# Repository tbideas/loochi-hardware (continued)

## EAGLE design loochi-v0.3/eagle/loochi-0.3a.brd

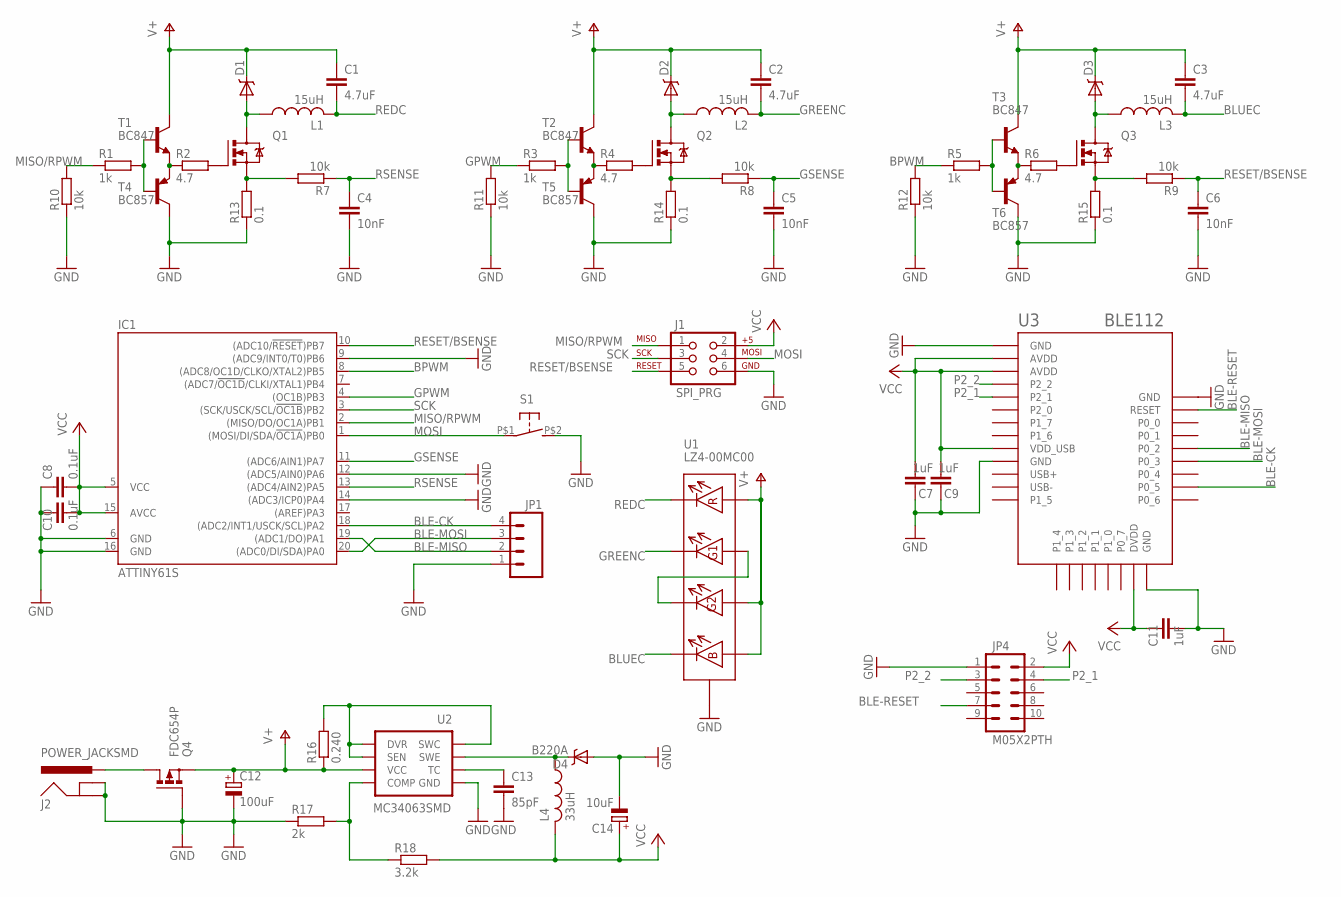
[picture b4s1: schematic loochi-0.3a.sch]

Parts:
C1, C2, C3: 4.7uF; C0805
C4, C5, C6: 10nF; C0805
C7, C9, C11: 1uF; C0805
C8, C10: 0.1uF; C0805
C12: 100uF; PANASONIC_D
C13: 85pF; C0805
C14: 10uF; UD-4X5,8_NICHICON
D1, D2, D3: PMEG4010CEH; SOD123F
D4: B220A; SMA-DIODE-BIG
IC1: ATTINY61S; SO20L
J1: SPI_PRG; 2X3-NS
J2: POWER_JACKSMD; POWER_JACK_SMD
JP1: M04PTH; 1X04
JP4: M05X2PTH; AVR_ICSP
L1, L2, L3: 15uH; BOURNS-6045
L4: 33uH; BOURNS-6045
Q1, Q2, Q3: PMN25ENSOT457; SOT457
Q4: FDC654P; SUPERSOT6
R1, R3, R5: 1k; R0805
R2, R4, R6: 4.7; R0805
R7, R8, R9, R10, R11, R12: 10k; R0805
R13, R14, R15: 0.1; R0805
R16: 0.240; R0805
R17: 2k; R0805
R18: 3.2k; R0805
S1: ALPS-SKRK39X29; ALPS-SKRK-39X29
T1, T2, T3: BC847; SOT23
T4, T5, T6: BC857; SOT23-BEC
U1: LZ4-00MC00
U2: MC34063SMD; SO08
U3: BLE112; SF-BLUEGIGA_BLE112-A

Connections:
BLE-CK: IC1.18 ((ADC2/INT1/USCK/SCL)PA2), JP1.4, U3.P0_5
BLE-MISO: IC1.19 ((ADC1/DO)PA1), JP1.2, U3.P0_2
BLE-MOSI: IC1.20 ((ADC0/DI/SDA)PA0), JP1.3, U3.P0_3
BLE-RESET: JP4.7, U3.RESET
BLUEC: C3.2, L3.P$2 (2), U1.P$8
BPWM: IC1.8 ((ADC8/OC1D/CLKO/XTAL2)PB5), R5.1, R12.2
GND: C4.2, C5.2, C6.2, C7.1, C8.1, C9.1, C10.1, C11.2, C12.-, C13.2, C14.-, D4.A, IC1.6 (GND), IC1.9 ((ADC9/INT0/T0)PB6), IC1.12 ((ADC5/AIN0)PA6), IC1.14 ((ADC3/ICP0)PA4), IC1.16 (GND), J1.6, J2.GND (GNDBREAK), J2.P$4 (GND), JP1.1, JP4.1, Q4.P$3 (G), R10.1, R11.1, R12.1, R13.1, R14.1, R15.1, R17.1, S1.P$2 (S), T4.C, T5.C, T6.C, U1.THERMAL, U1.THERMAL-VIA (THERMAL), U1.THERMAL-VIA2 (THERMAL), U2.4 (GND), U3.GND1 (GND), U3.GND2 (GND), U3.GND3 (GND), U3.GND4 (GND)
GPWM: IC1.4 ((OC1B)PB3), R3.1, R11.2
GREENC: C2.2, L2.P$2 (2), U1.P$6
GSENSE: C5.1, IC1.11 ((ADC6/AIN1)PA7), R8.1
MISO/RPWM: IC1.2 ((MISO/DO/OC1A)PB1), J1.1, R1.1, R10.2
MOSI: IC1.1 ((MOSI/DI/SDA/!OC1A!)PB0), J1.4, S1.P$1
unnamed: U1.P$1, U1.P$5
unnamed: R2.1, T1.2 (E), T4.E
unnamed: R1.2, T1.1 (B), T4.B
unnamed: Q1.P$3 (G), R2.2
unnamed: Q1.P$4 (S), R7.2, R13.2
unnamed: D1.P$A (A), L1.P$1 (1), Q1.P$1 (D), Q1.P$2 (D), Q1.P$5 (D), Q1.P$6 (D)
unnamed: R4.1, T2.2 (E), T5.E
unnamed: J2.VIN0 (PWR), J2.VIN1 (PWR), Q4.P$1 (D), Q4.P$2 (D), Q4.P$5 (D), Q4.P$6 (D)
unnamed: R3.2, T2.1 (B), T5.B
unnamed: Q2.P$3 (G), R4.2
unnamed: D2.P$A (A), L2.P$1 (1), Q2.P$1 (D), Q2.P$2 (D), Q2.P$5 (D), Q2.P$6 (D)
unnamed: R16.2, U2.1 (SWC), U2.7 (SEN), U2.8 (DVR)
unnamed: Q2.P$4 (S), R8.2, R14.2
unnamed: C13.1, U2.3 (TC)
unnamed: R6.1, T3.2 (E), T6.E
unnamed: R5.2, T3.1 (B), T6.B
unnamed: Q3.P$3 (G), R6.2
unnamed: D3.P$A (A), L3.P$1 (1), Q3.P$1 (D), Q3.P$2 (D), Q3.P$5 (D), Q3.P$6 (D)
unnamed: D4.C, L4.P$1 (1), U2.2 (SWE)
unnamed: Q3.P$4 (S), R9.2, R15.2
unnamed: R17.2, R18.1, U2.5 (COMP)
P2_1: JP4.4, U3.P2_1
P2_2: JP4.3, U3.P2_2
REDC: C1.2, L1.P$2 (2), U1.P$4
RESET/BSENSE: C6.1, IC1.10 ((ADC10/!RESET!)PB7), J1.5, R9.1
RSENSE: C4.1, IC1.13 ((ADC4/AIN2)PA5), R7.1
SCK: IC1.3 ((SCK/USCK/SCL/!OC1B!)PB2), J1.3
V+: C1.1, C2.1, C3.1, C12.+, D1.P$C (C), D2.P$C (C), D3.P$C (C), Q4.P$4 (S), R16.1, T1.3 (C), T2.3 (C), T3.3 (C), U1.P$2, U1.P$3, U1.P$7, U2.6 (VCC)
VCC: C7.2, C8.2, C9.2, C10.2, C11.1, C14.+, IC1.5 (VCC), IC1.15 (AVCC), J1.2, JP4.2, L4.P$2 (2), R18.2, U3.AVDD1 (AVDD), U3.AVDD2 (AVDD), U3.DVDD, U3.VDD_USB

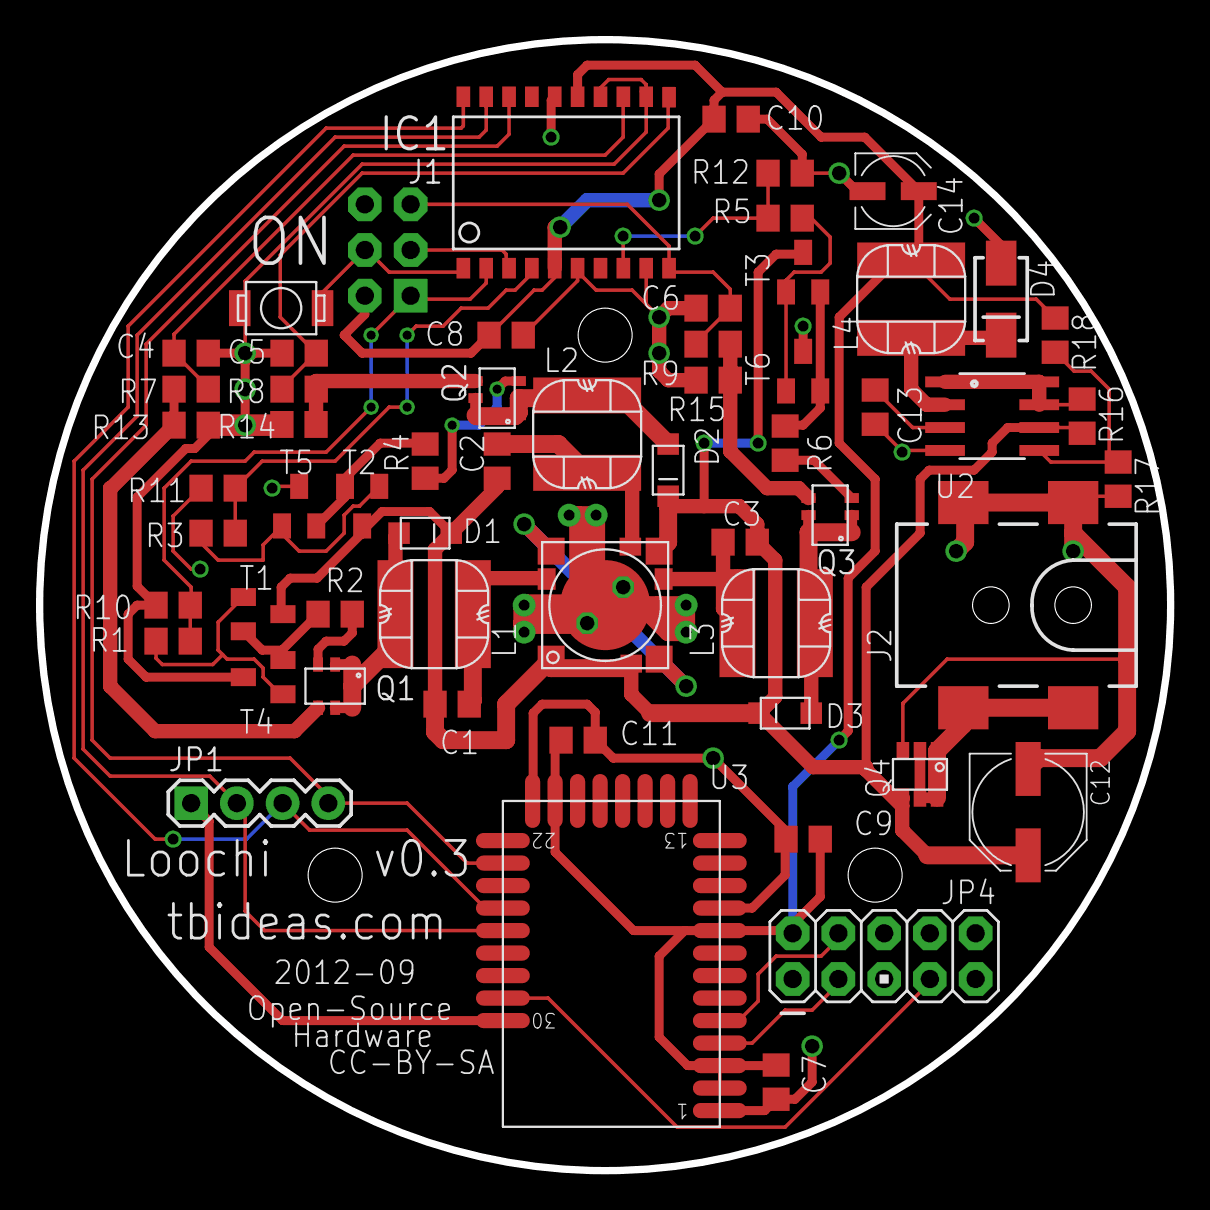
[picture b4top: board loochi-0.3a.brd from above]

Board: 2 copper layers, 62.8 x 62.8 mm, 59 parts (0 on the bottom side), 41 nets.

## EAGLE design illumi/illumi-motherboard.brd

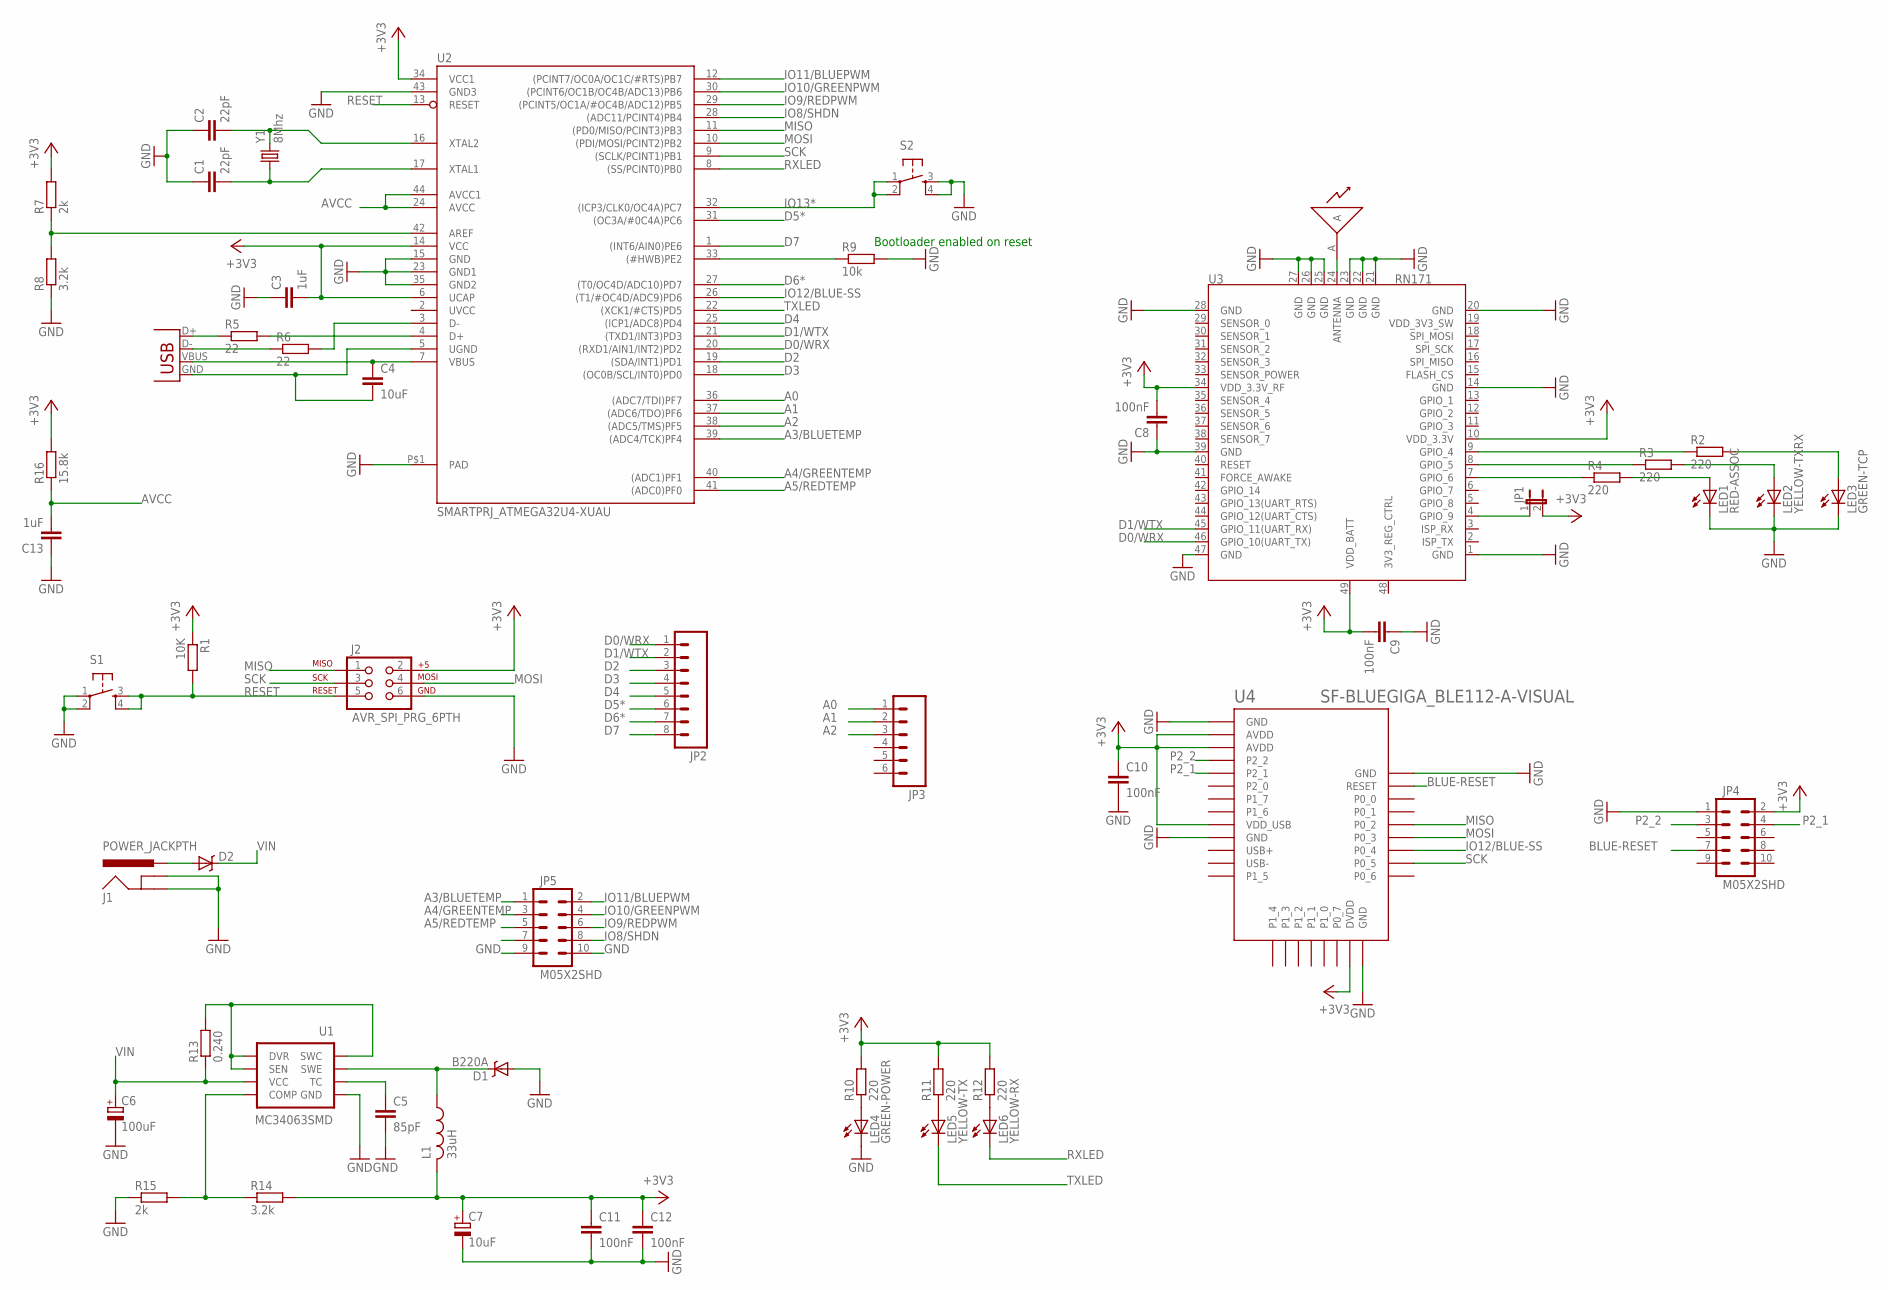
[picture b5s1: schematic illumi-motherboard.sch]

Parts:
A1: ANTENNAWIRE; ANTENNA-WIRE
C1, C2: 22pF; C0805
C3, C13: 1uF; C0805
C4: 10uF; C0805
C5: 85pF; C0805
C6: 100uF; PANASONIC_D
C7: 10uF; SMC_C
C8, C9, C10, C11, C12: 100nF; C0805
D1: B220A; SMA-DIODE-BIG
D2: DIODE-SCHOTTKYBIGPAD; SMA-DIODE-BIG
J1: POWER_JACKPTH; POWER_JACK_PTH
J2: AVR_SPI_PRG_6PTH; 2X3
JP1: JUMPER-2PTH; 1X02
JP2: M081X08; 1X08
JP3: M06FEMALE_LOCK; 1X06_FEMALE_LOCK.010
JP4, JP5: M05X2SHD; 2X5-SHROUDED
L1: 33uH; BOURNS-6045
LED1: RED-ASSOC; SML0805
LED2: YELLOW-TXRX; SML0805
LED3: GREEN-TCP; SML0805
LED4: GREEN-POWER; SML0805
LED5: YELLOW-TX; SML0805
LED6: YELLOW-RX; SML0805
R1: 10K; R0805
R2, R3, R4, R10, R11, R12: 220; R0805
R5, R6: 22; R0805
R7, R15: 2k; R0805
R8, R14: 3.2k; R0805
R9: 10k; R0805
R13: 0.240; R1206
R16: 15.8k; R0805
S1, S2: TAC_SWITCHB3FS; OMRON-B3FS
U1: MC34063SMD; SO08
U2: SMARTPRJ_ATMEGA32U4-XUAU; SMARTPRJ_TQFP44-PAD
U3: RN171; MODULE_49P-1.27-26.67X17.78
U4: SF-BLUEGIGA_BLE112-A-VISUAL; SF-BLUEGIGA_BLE112-A
X1: USB-MICROB
Y1: 8Mhz; HC49US

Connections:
+3V3: C3.2, C7.+, C8.2, C9.2, C10.1, C11.1, C12.1, J2.2, JP1.2, JP4.2, L1.P$2 (2), R1.1, R7.2, R10.2, R11.2, R12.2, R14.2, R16.2, U2.6 (UCAP), U2.14 (VCC), U2.34 (VCC1), U3.10 (VDD_3.3V), U3.34 (VDD_3.3V_RF), U3.49 (VDD_BATT), U4.AVDD1 (AVDD), U4.AVDD2 (AVDD), U4.DVDD, U4.VDD_USB
A0: JP3.1, U2.36 ((ADC7/TDI)PF7)
A1: JP3.2, U2.37 ((ADC6/TDO)PF6)
A2: JP3.3, U2.38 ((ADC5/TMS)PF5)
A3/BLUETEMP: JP5.1, U2.39 ((ADC4/TCK)PF4)
A4/GREENTEMP: JP5.3, U2.40 ((ADC1)PF1)
A5/REDTEMP: JP5.5, U2.41 ((ADC0)PF0)
AVCC: C13.2, R16.1, U2.24 (AVCC), U2.44 (AVCC1)
BLUE-RESET: JP4.7, U4.RESET
D0/WRX: JP2.1, U2.20 ((RXD1/AIN1/INT2)PD2), U3.46 (GPIO_10(UART_TX))
D1/WTX: JP2.2, U2.21 ((TXD1/INT3)PD3), U3.45 (GPIO_11(UART_RX))
D2: JP2.3, U2.19 ((SDA/INT1)PD1)
D3: JP2.4, U2.18 ((OC0B/SCL/INT0)PD0)
D4: JP2.5, U2.25 ((ICP1/ADC8)PD4)
D5*: JP2.6, U2.31 ((OC3A/#0C4A)PC6)
D6*: JP2.7, U2.27 ((T0/OC4D/ADC10)PD7)
D7: JP2.8, U2.1 ((INT6/AIN0)PE6)
GND: C1.1, C2.1, C3.1, C5.2, C6.-, C7.-, C8.1, C9.1, C10.2, C11.2, C12.2, C13.1, D1.A, J1.GND, J1.GNDBREAK, J2.6, JP4.1, JP5.9, JP5.10, LED1.C, LED2.C, LED3.C, LED4.C, R8.1, R9.2, R15.1, S1.1, S1.2, S2.3, S2.4, U1.4 (GND), U2.15 (GND), U2.23 (GND1), U2.35 (GND2), U2.43 (GND3), U2.P$1 (PAD), U3.1 (GND), U3.14 (GND), U3.20 (GND), U3.21 (GND), U3.22 (GND), U3.23 (GND), U3.25 (GND), U3.26 (GND), U3.27 (GND), U3.28 (GND), U3.39 (GND), U3.47 (GND), U4.GND1 (GND), U4.GND2 (GND), U4.GND3 (GND), U4.GND4 (GND)
IO8/SHDN: JP5.8, U2.28 ((ADC11/PCINT4)PB4)
IO9/REDPWM: JP5.6, U2.29 ((PCINT5/OC1A/#OC4B/ADC12)PB5)
IO10/GREENPWM: JP5.4, U2.30 ((PCINT6/OC1B/OC4B/ADC13)PB6)
IO11/BLUEPWM: JP5.2, U2.12 ((PCINT7/OC0A/OC1C/#RTS)PB7)
IO12/BLUE-SS: U2.26 ((T1/#OC4D/ADC9)PD6), U4.P0_4
IO13*: S2.1, S2.2, U2.32 ((ICP3/CLK0/OC4A)PC7)
MISO: J2.1, U2.11 ((PD0/MISO/PCINT3)PB3), U4.P0_2
MOSI: J2.4, U2.10 ((PDI/MOSI/PCINT2)PB2), U4.P0_3
unnamed: LED4.A, R10.1
unnamed: A1.A, U3.24 (ANTENNA)
unnamed: R2.1, U3.9 (GPIO_4)
unnamed: R3.1, U3.8 (GPIO_5)
unnamed: R4.1, U3.7 (GPIO_6)
unnamed: LED1.A, R4.2
unnamed: LED2.A, R3.2
unnamed: LED3.A, R2.2
unnamed: C4.2, U2.5 (UGND), X1.GND
unnamed: R5.1, X1.D+
unnamed: JP1.1, U3.4 (GPIO_9)
unnamed: R6.1, X1.D-
unnamed: C4.1, U2.7 (VBUS), X1.VBUS
unnamed: R5.2, U2.4 (D+)
unnamed: R6.2, U2.3 (D-)
unnamed: R7.1, R8.2, U2.42 (AREF)
unnamed: LED5.A, R11.1
unnamed: LED6.A, R12.1
unnamed: R9.1, U2.33 ((#HWB)PE2)
unnamed: R13.2, U1.1 (SWC), U1.7 (SEN), U1.8 (DVR)
unnamed: D1.C, L1.P$1 (1), U1.2 (SWE)
unnamed: C5.1, U1.3 (TC)
unnamed: R14.1, R15.2, U1.5 (COMP)
unnamed: D2.A, J1.PWR
P2_1: JP4.4, U4.P2_1
P2_2: JP4.3, U4.P2_2
RESET: J2.5, R1.2, S1.3, S1.4, U2.13 (RESET)
RXLED: LED6.C, U2.8 ((SS/PCINT0)PB0)
SCK: J2.3, U2.9 ((SCLK/PCINT1)PB1), U4.P0_5
TXLED: LED5.C, U2.22 ((XCK1/#CTS)PD5)
UVCC: U2.2 (UVCC)
VIN: C6.+, D2.C, R13.1, U1.6 (VCC)
XTAL1: C1.2, U2.17 (XTAL1), Y1.1
XTAL2: C2.2, U2.16 (XTAL2), Y1.2

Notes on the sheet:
Bootloader enabled on reset

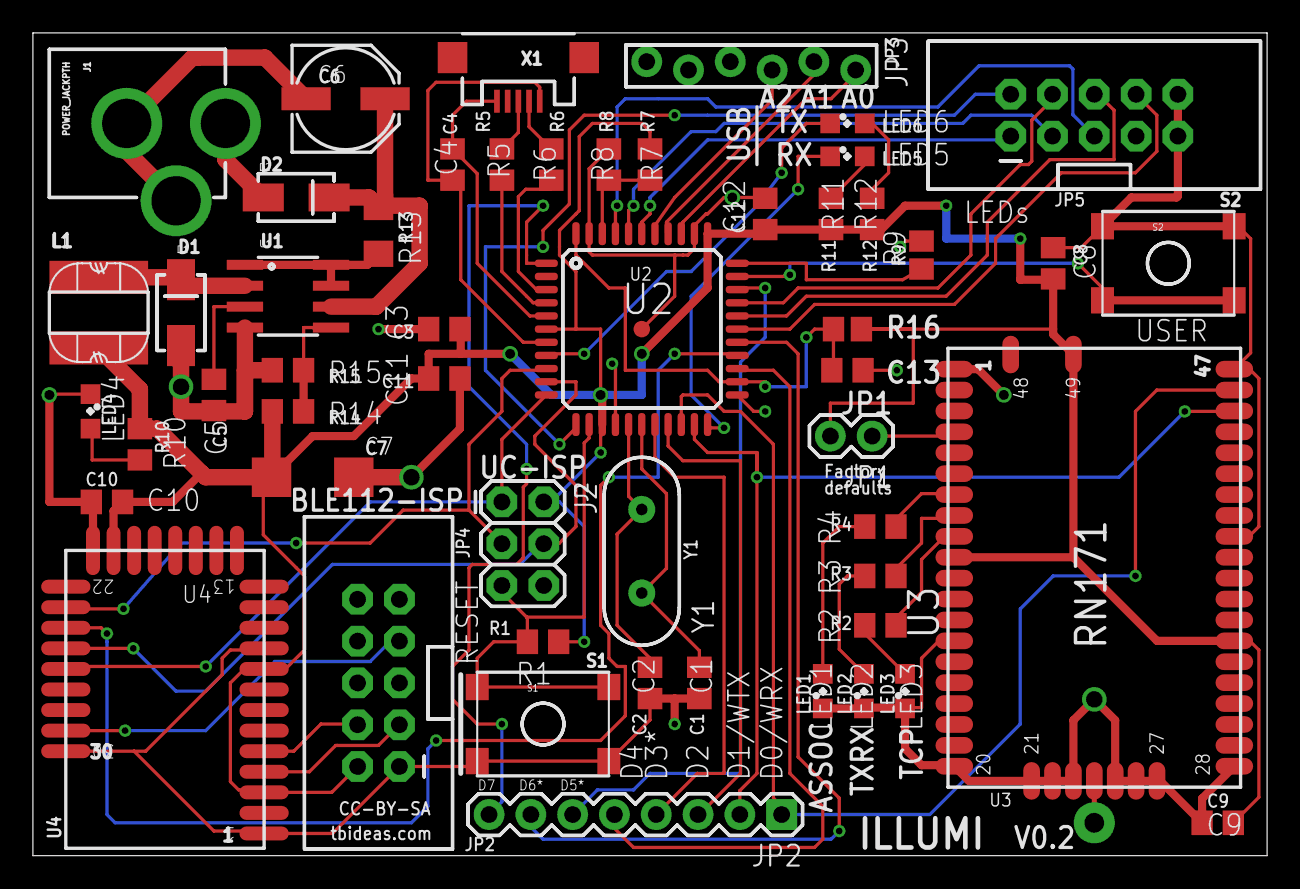
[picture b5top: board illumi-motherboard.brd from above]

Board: 2 copper layers, 75.0 x 50.0 mm, 54 parts (0 on the bottom side), 59 nets.

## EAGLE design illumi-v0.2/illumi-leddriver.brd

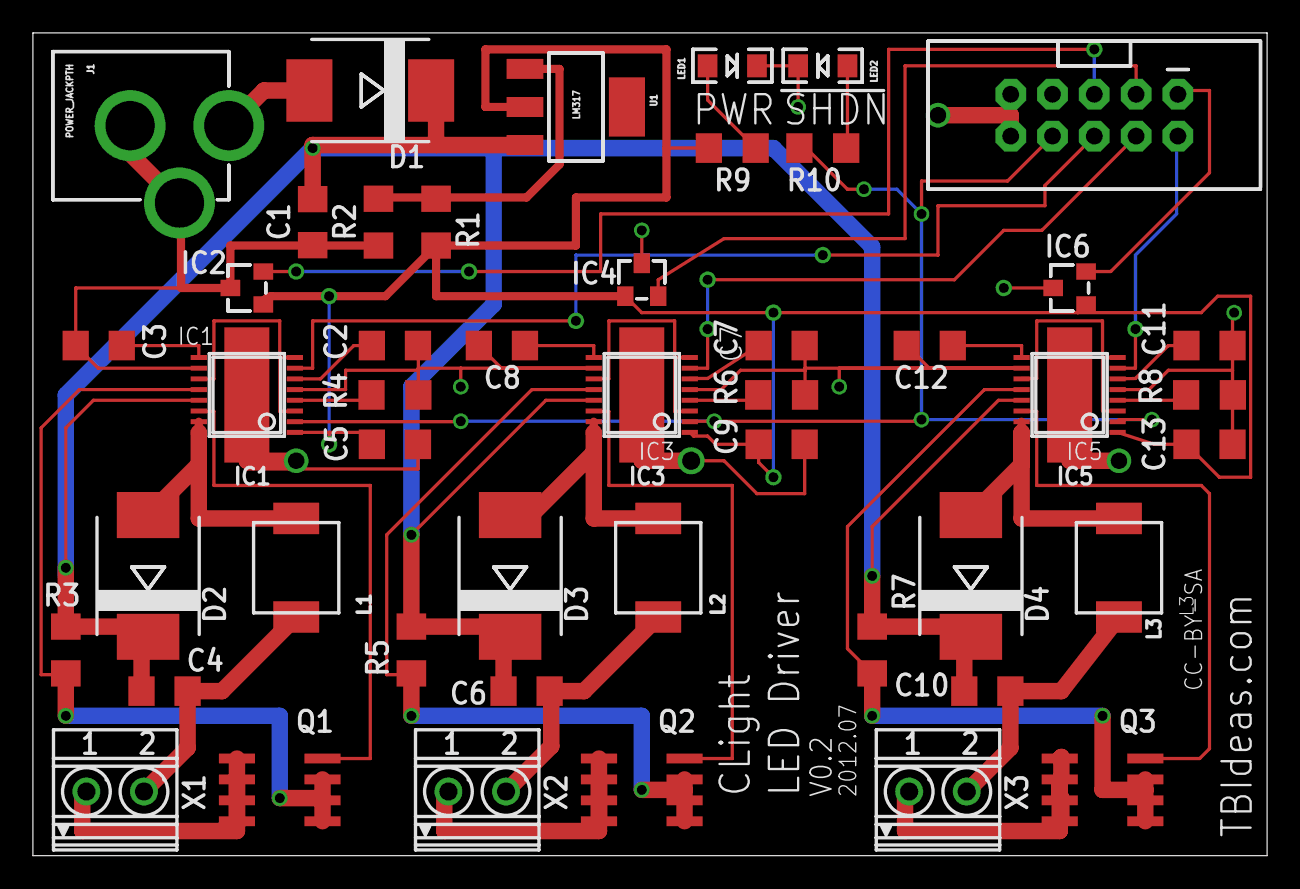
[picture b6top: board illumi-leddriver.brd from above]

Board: 2 copper layers, 75.0 x 50.0 mm, 47 parts (0 on the bottom side), 41 nets.

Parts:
C1, C2, C3, C7, C8, C11, C12: 0.1uF; C1206
C4, C6, C10: 10uF; C1206
C5, C9, C13: 2.2uF; C1206
D1: 50V-8A; SMC
D2, D3, D4: MBRS360T3; SMC
IC1, IC3, IC5: LT3518TSSOP16-EXPOSED-PAD-LARGE; TSSOP16-EXPOSED_PAD_LARGE
IC2, IC4, IC6: TC1047; SOT-23B
J1: POWER_JACKPTH; POWER_JACK_PTH
JP1: M05X2SHD; 2X5-SHROUDED
L1, L2, L3: 15uH; L2020
LED1: Green; LED-1206
LED2: red; LED-1206
Q1, Q2, Q3: FDS4685; SO-08
R1: 240; R1206
R2: 390; R1206
R3, R5, R7: 143mO; R1206
R4, R6, R8: 16.9kO; R1206
R9, R10: 220; R1206
U1: LM317; SOT223
X1, X2, X3: 1751248

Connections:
3.3V: C5.1, C9.1, C13.1, IC1.1, IC2.1, IC3.1, IC4.1, IC5.1, IC6.1, R1.2, R9.2, U1.2
BLUEPWM: IC5.7, JP1.2
BLUETEMP: IC6.2, JP1.1
GND: C1.2, C2.2, C3.2, C5.2, C7.2, C8.2, C9.2, C11.2, C12.2, C13.2, IC1.5, IC1.10, IC1.GND, IC2.3, IC3.5, IC3.10, IC3.GND, IC4.3, IC5.5, IC5.10, IC5.GND, IC6.3, J1.GND, J1.GNDBREAK, JP1.9, JP1.10, LED1.C, LED2.C, R2.1, R4.1, R6.1, R8.1
GREENPWM: IC3.7, JP1.4
GREENTEMP: IC4.2, JP1.3
unnamed: IC1.3, IC1.8, IC1.11
unnamed: IC3.3, IC3.8, IC3.11
unnamed: R1.1, R2.2, U1.1
unnamed: IC3.12, Q2.1, Q2.2, Q2.3, R5.2
unnamed: IC1.12, Q1.1, Q1.2, Q1.3, R3.2
unnamed: IC1.14, Q1.4
unnamed: Q1.5, Q1.6, Q1.7, Q1.8, X1.1
unnamed: C4.2, L1.P$2, X1.2
unnamed: D2.A, IC1.15, IC1.16, L1.P$1
unnamed: IC3.14, Q2.4
unnamed: IC1.4, R4.2
unnamed: Q2.5, Q2.6, Q2.7, Q2.8, X2.1
unnamed: C6.2, L2.P$2, X2.2
unnamed: D3.A, IC3.15, IC3.16, L2.P$1
unnamed: C2.1, IC1.6
unnamed: C3.1, IC1.9
unnamed: IC3.4, R6.2
unnamed: C7.1, IC3.6
unnamed: C8.1, IC3.9
unnamed: IC5.3, IC5.8, IC5.11
unnamed: IC5.12, Q3.1, Q3.2, Q3.3, R7.2
unnamed: IC5.14, Q3.4
unnamed: Q3.5, Q3.6, Q3.7, Q3.8, X3.1
unnamed: C10.2, L3.P$2, X3.2
unnamed: D4.A, IC5.15, IC5.16, L3.P$1
unnamed: IC5.4, R8.2
unnamed: C11.1, IC5.6
unnamed: C12.1, IC5.9
unnamed: D1.A, J1.PWR
unnamed: LED1.A, R9.1
unnamed: LED2.A, R10.1
REDPWM: IC1.7, JP1.6
REDTEMP: IC2.2, JP1.5
SHDN: IC1.2, IC3.2, IC5.2, JP1.8, R10.2
VIN: C1.1, C4.1, C6.1, C10.1, D1.C, D2.C, D3.C, D4.C, IC1.13, IC3.13, IC5.13, R3.1, R5.1, R7.1, U1.3

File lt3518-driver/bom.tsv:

SubCircuit	Part	Description	Package	Mouser Ref	Manufacturer	Mfr Ref	Qty	PU (1)	PU (Reel)	Reel Qty
Led	LEDENGIN1	LZC	MPCB	897-LZC83MC00	LedEngin	LZC-83MC00	1	$37.70	33.410	100
Led Driver	U1	LM317 Power regulator	SOT-223	595-LM317DCYR	Texas Instruments	LM317DCYR	1	$0.62	0.247	2500
Led Driver	J1	Power Jack - 2.5mm		806-KLDHCX-0202-BC	KYCON	        KLDHCX-0202-BC	1	$0.89	0.620	1000
	J1'	Power Jack - 2.5mm		1710-0725	Kobiconn	1710-0725	1	$1.28	0.550	5000
Led Driver	R1	240 Ohm	1206	660-RK73B2BTTD241J	KOA Speer	RK73B2BTTD241J	1	$0.08	0.009	5000
Led Driver	R2	390 Ohm	1206	660-RK73B2BTTDD391J	KOA Speer	RK73B2BTTDD391J	1	$0.08	0.008	10000
Led Driver	C1	0.1uF >50V	1206	81-GRM319F51H104ZA	Murata	GRM319F51H104ZA01D	1	$0.09	0.026	4000
Led Driver	JP1	0.1" pitch 2x5 connector plastic shoulder		737-BHR-10-VUA	ADAM TECH	BHR-10-VUA	1	$0.28	0.180	1000
Led Driver	D1	Rectifier Diode 800V 8A	SMC	621-S8KC-13	Diodes Inc	S8KC-13	1	$0.46	0.196	3000
Led Driver	LED1	Green Led	1206	720-LGN971-KN-1	OSRAM Opto Semicond.	LG N971-KN-1	1	$0.10	0.052	4000
Led Driver	LED2	Red Led	1206	720-LHN974-KN-1	OSRAM Opto Semicond.	LH N974-KN-1	1	$0.12	0.052	12000
Led Driver	R9,R10	220 Ohm	1206	660-RK73B2BTTDD221J	KOA Speer	RK73B2BTTDD221J	2	$0.08	0.008	10000
Led Driver - Chan	IC1,IC3,IC5	LT3518	TSSOP	Buy direct from LINEAR TECH	LINEAR TECHNOLOGY	LT3518	3	$4.43	3.760	100
Led Driver - Chan	Q1,Q2,Q3	P-MOSFET	SOIC-8 Narrow	512-FDS4685	Fairchild Semi	FDS4685	3	$0.82	0.345	2500
Led Driver - Chan	D2,D3,D4	Schottky 3A 60V	SMC	863-MBRS360T3G	ON Semiconductor	MBRS360T3G	3	$0.62	0.201	2500
Led Driver - Chan	L1,L2,L3	15 uH Power Inductance (max sat 2A)		70-IHLP2020CZER150M0	Vishay/Dale	IHLP2020CZER150M01	3	$2.29	1.110	2000
Led Driver - Chan	R3,R5,R7	Current Sense resistor 143 mOhm 1206	1206	660-SR732BTTER143F	KOA Speer	SR732BTTER143F	3	$0.43	0.250	4000
Led Driver - Chan	R4,R6,R8	16.9kOhm	1206	660-RK73H2BTTD1692F	KOA Speer	RK73H2BTTD1692F	3	$0.08	0.015	5000
Led Driver - Chan	C2,C3,C7,C8,C11,C12	0.1uF 10V	1206	810-CGA5L4X7T2W104KS	TDK	CGA5L4X7T2W104K/SOFT	6	$0.27	0.149	2000
Led Driver - Chan	C4,C6,C10	10uF 50V X5R	1206	810-CGA5L3X5R1H106K	TDK	CGA5L3X5R1H106K	3	$0.57	0.311	2000
Led Driver - Chan	C5,C9,C13	2.2uF	1206	81-GRM31MF51H225ZA1L  	Murata	GRM31MF51H225ZA01L	3	$0.21	0.070	3000
Led Driver - Chan	X1,X2,X3	Phoenix Connector 3.5mm 2 contacts		651-1984617	Phoenix Contact	1984617	3	$0.38	0.248	500
Led Driver	IC2,IC4,IC6	TC1047A	SOT-23B-3	579-TC1047AVNBTR	Microchip Technology	TC1047AVNBTR	3	$0.66	0.470	3000
										
										
										
										
										
										
										
										
										
										
										
										
										
										
										
										
Total Price								74.95	56.6

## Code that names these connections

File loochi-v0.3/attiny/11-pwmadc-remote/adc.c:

#include <avr/io.h>
#include <avr/pgmspace.h>
#include "globals.h"

/* ADC configuration for each sense resistor */
#define ADMUX_RED    	((1 << REFS1) | 0x12) // Pins PA5(-) and PA4(+) with a gain of 20x
#define ADMUX_GREEN  	((1 << REFS1) | 0x17) // Pins PA7(-) and PA6(+) with a gain of 20x
#define ADMUX_BLUE   	((1 << REFS1) | 0x19) // Pins PB5(-) and PB6(+) with a gain of 20x

uint8_t adc_discard;

/*
 * Truthtable to choose which channel the ADC should read next.
 * Input: 6bits
 *  00XXXXXX
 *    ++     -> previous selected channel (00=red, 01=green, 10=blue)
 *      +    -> have we got a valid reading on this channel already
 *       +   -> is red on
 *        +  -> is green on
 *         + -> is blue on
 * Output: next value of ADMUX or 0 if no new ADC is to be chosen
 */
PROGMEM uint8_t ADC_TRUTHTABLE[] = {
	0,ADMUX_BLUE,ADMUX_GREEN,ADMUX_GREEN,ADMUX_RED,ADMUX_RED,ADMUX_RED,ADMUX_RED,0,ADMUX_BLUE,ADMUX_GREEN,ADMUX_GREEN,ADMUX_RED,
	ADMUX_BLUE,ADMUX_GREEN,ADMUX_GREEN,0,ADMUX_BLUE,ADMUX_GREEN,ADMUX_GREEN,ADMUX_RED,ADMUX_BLUE,ADMUX_GREEN,ADMUX_GREEN,0,
	ADMUX_BLUE,ADMUX_GREEN,ADMUX_BLUE,ADMUX_RED,ADMUX_BLUE,ADMUX_RED,ADMUX_BLUE,0,ADMUX_BLUE,ADMUX_GREEN,ADMUX_BLUE,ADMUX_RED,
	ADMUX_BLUE,ADMUX_RED,ADMUX_BLUE,0,ADMUX_BLUE,ADMUX_GREEN,ADMUX_GREEN,ADMUX_RED,ADMUX_RED,ADMUX_RED,ADMUX_RED
};

/* Expected reading of the ADC for a given value of Ton to get 700mA on the LED
 * 
 * The formula is: ADC = 2*Ton/Tperiod*Iled*1024/2.56
 * Everything is known except Ton.
 * $ perl -e 'print join(",", map { sprintf "%.0f", (2*$_/0xff*0.7*1024/2.56)} 0..255)'
 * (the first value was manually hacked to -1 to make sure the thing starts)
 */
PROGMEM int16_t ADC_TARGET_VALUES[] = { 
	-1,2,4,7,9,11,13,15,18,20,22,24,26,29,31,33,35,37,40,42,44,46,48,51,53,55,57,59,61,64,66,68,70,72,75,77,79,81,83,86,88,90,92,94,97,99,101,103,105,
	108,110,112,114,116,119,121,123,125,127,130,132,134,136,138,141,143,145,147,149,152,154,156,158,160,163,165,167,169,171,173,176,178,180,182,184,
	187,189,191,193,195,198,200,202,204,206,209,211,213,215,217,220,222,224,226,228,231,233,235,237,239,242,244,246,248,250,253,255,257,259,261,264,
	266,268,270,272,275,277,279,281,283,285,288,290,292,294,296,299,301,303,305,307,310,312,314,316,318,321,323,325,327,329,332,334,336,338,340,343,
	345,347,349,351,354,356,358,360,362,365,367,369,371,373,376,378,380,382,384,387,389,391,393,395,397,400,402,404,406,408,411,413,415,417,419,422,
	424,426,428,430,433,435,437,439,441,444,446,448,450,452,455,457,459,461,463,466,468,470,472,474,477,479,481,483,485,488,490,492,494,496,499,501,
	503,505,507,509,512,514,516,518,520,523,525,527,529,531,534,536,538,540,542,545,547,549,551,553,556,558,560
};
#define ADC_TARGET(a) (pgm_read_word_near(ADC_TARGET_VALUES + a))

/* Count the number of values that we have discarded. 
 * Every time we switch from one channel to the other, we need to discard at least one
 * before trusting the reading.
 */
uint8_t adc_discard = 0;

/* Forward declaration */
uint8_t adc_choose_nextchannel(void);


/*
 * Configure the Analog-Digital Converter.
 */
void init_adc(void)
{
	/* Set the voltage reference to 2.56V and select a channel */
	ADMUX = ADMUX_RED;
	/* This bit needs to be set for the 2.56 Voltage reference */
	ADCSRB = (1 << REFS2); // 2.56
	//ADCSRB = 0; // 1.1
	//ADCSRB |= (1 << GSEL); // x32
	/* Test results: 
	 *   Blue led, current = 708 mA (pwm=127) - Approximately 1000 samples each time, repeated several times.
	 *   1.1  & x20 => Std deviation=1.45 
	 *   1.1  & x32 => Std deviation=11/14  (@pwm=100/487mA to avoid overflow) 
	 *   2.56 & x20 => Std deviation=.57/.66 
	 *   2.56 & x32 => Std deviation=23/25 
	 *
	 * Conclusion: Avoid x32 (maybe that's why it is not listed in the doc for our pins configuration?)
	 */

	/* Set the prescaler to DIV64. The ADC clock will run @125kHz 
	 * which is in the recommended range (50kHz to 200kHz).
	 * 1 ADC clockcycle will be 8uS.
	 * Sampling will be done 1.5 cycles * 8uS = 12uS after the start of a conversion.
	 * Result will be available 13 cycles * 8us = 104uS after the start of a conversion.
	 */
	ADCSRA = (1 << ADPS2) | (1 << ADPS1)
	/* Enable interrupts for ADC result */
		| (1 << ADIE)
	/* Enable the ADC */
		| (1 << ADEN);
}

/* 
 * This function checks to see if the ADS is available and starts a new conversion on the right channel.
 */
void adc_loop()
{
	/* 
	 * If the ADC is available, and if the signals have been on for at least a few cycles, 
	 * then we can choose one channel and run a conversion.
	 */
	if ((ADCSRA & (1 << ADSC)) == 0) {
		/* Choosing the right channel is actually pretty complicated so we use a truth table */
		uint8_t next_channel = adc_choose_nextchannel();
		
		if (next_channel == ADMUX) {
			/* We stay on the same ADC channel - Just restart a new conversion */
			ADCSRA |= (1 << ADSC);
		}
		else if (next_channel != 0) {
			/* Change of ADC channel. We will need to discard. */
			adc_discard = 0;
			ADMUX = next_channel;
		}
	}
}

/* 
 * Calculate the input to the truth table (read description above). 
 * 
 * Returns 0 if no ADC should be chosen or the ADMUX value to use.
 */
uint8_t adc_choose_nextchannel(void)
{
	uint8_t truth;
	if (ADMUX == ADMUX_RED)		truth = 0x00;
	if (ADMUX == ADMUX_GREEN)	truth = 0x10;
	if (ADMUX == ADMUX_BLUE)	truth = 0x20;

	if (adc_discard > 1) 
		truth |= 0x8;
	
	// Red, Green and Blue always on (we have removed the brightness pwm)
	truth |= 0x7;
	
	return pgm_read_word_near(ADC_TRUTHTABLE + truth);
}

void process_adc_reading(uint16_t adc)
{
	if (adc_discard++ < 1)
		return;

	if (ADMUX == ADMUX_RED) 
		redadc = adc;
	else if (ADMUX == ADMUX_GREEN) 
		greenadc = adc;
	else if (ADMUX == ADMUX_BLUE) 
		blueadc = adc;
}

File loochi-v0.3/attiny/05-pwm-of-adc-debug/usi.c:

/*
 * usi.c
 * 
 * Library to use the USI on AtTiny861
 * 
 * Copyright 2012 - Thomas Sarlandie - TBIdeas
 * Distributed under the CC-BY-SA license.
 * http://creativecommons.org/licenses/by-sa/3.0/
 */

#include <avr/io.h>
#include "usi.h"

void spi_master_init(uint8_t port)
{
	if (port == USI_PORTB) 
	{
		DDRB |= (1 << PB1) | (1 << PB2);
	}
	else if (port == USI_PORTA) 
	{
		DDRA |= (1 << PA1) | (1 << PA2);
		USIPP = 1;
	}
}

uint8_t spi_master_write(uint8_t byte)
{
	USIDR = byte;
	USISR = 1<<USIOIF; // clear counter overflow flag
 
	// tick the clock until the overflow is reached again
  while ( (USISR & _BV(USIOIF)) == 0 ) {
   	USICR = (1<<USIWM0)|(1<<USICS1)|(1<<USICLK)|(1<<USITC);
  }
	// return the value sent by the slave
  return USIDR;
}

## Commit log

2012-07-17 Adding file as they were submitted to Laen PCB order
2012-07-17 Adding bom
2012-07-26 Adding v0.2 files for motherboard - sent to fab
2012-08-23 Adding files for v0.0/v0.1/v0.2
2012-08-23 Adding readme - some cleaning up (more to come)
2012-08-23 More cleanup + Adding LTSpice file
2012-09-14 First commit of attiny work
2012-10-02 long time due commit with 0.3 and 0.4 and lots of work on the firmware
2012-10-03 SPI slave working
2012-10-04 SPI-slave working with 3 bytes messages and re-synchronization with sender (based on timeout)
2012-10-04 Adding BLE112 firmware
2012-10-04 Adding gitignore for ble112 directory
2012-10-05 For the first time, this firmware is able to control three channels. I have only tested one but there is no reason that the two others should not work. This is a major step forward! Also done a lot o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
2012-10-10 Code works on the real board
2012-10-12 Better default start values
2012-10-12 Fix turn off the light on startup
2012-10-26 Adding bom to loochi 0.4
2012-10-26 Max period of signal is now 0x00FF to deal with some flickering. BLE now requires write (instead of write_without_response) so that the app can adjust the write speed to the actual transmission speed.
2012-10-26 Updating README with description of 0.3/0.4
2012-10-31 Adding STL files for latest version of the shade and plastic enclosing
2012-10-31 Adding v10 of the firmware with support of the hardware button (ooh-yeah!)
2012-10-31 Button turns the light on and off
2012-10-31 Plastic design version E for SLA
2012-11-01 Removing some .DS_Store files and adding .DS_Store to the gitignore
2012-11-06 Added program 11-pwmadc-remote which allows full external control of the RED current PWM through the SPI interface and reading back the ADC values.
    This is useful to make sure that the ADC is working properly and to check the math that we use to convert ADC reading into actual current in the LED.
2012-11-15 Adding base Loochi 0.5 files
2012-11-15 Finalized board layout but have not run DRC yet.
2012-11-19 loochi-0.5.brd
2012-11-19 Continued work on board v0.5 - Integrated Jurgen v0.5.1 changes - Shielded bsense - Holes for lenses - drc ok now
    Next steps: BOM & check parts footprint
2012-11-19 More work on the board - almost final (antenna trace needs rework)
2012-11-21 Commiting board 0.5 as ordered from Oshpark.com
2012-11-21 Adding OpenOffice file for inductor size estimation
2012-11-21 Adding CAM job file used to generate gerbers
2012-11-23 Moved two traces to match Sunstone PCB guidelines
2012-12-04 First draft of Loochi 0.6 - Back to BLE112 module - New power connector layout - New switch layout - One diode to make sure that the programmers can not provide power to the led - Another diode to pr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
2013-01-02 One major fix (vias under the cpu removed) + minor adjustments
    * Removed all vias under the CPU
    * Fix holes for the lense
    * Fix size of power supply tab
    * Connect the button to the BLE Module
2013-01-02 Routed connections + Added SPI on BLE connector + Some cleaning/Rework
2013-01-06 Final changes before ordering the board (minor cosmetic changes)
2013-01-15 Fixing reference of F1 (we want a 0603)
2013-01-15 Starting software work on 0.6
2013-01-15 remove .ds_store
2013-01-15 Changed f-pwm to 250khz
2013-01-15 Switched to 250khz - Added adc test results
2013-01-15 Adding laen pcb files (gerber + render) for loochi 0.6
2013-01-15 Adding ble112 files for loochi 0.6
2013-01-15 Adding pdf schema
2013-04-09 Commiting working firmware for loochi 0.6 (based on loochi-0.3/10)
2013-04-09 Added support for the Chip Select wire
2013-04-09 Added support Chip Select
2013-04-09 Update to latest SDK + Support write with/without response
2013-04-09 PCB 0.6b with some extra labels on the board for SPI debugging
2013-04-09 adding first try at remodeling loochi in inventor fusion - not done at all ...
2016-01-23 Commiting modified files on laptop before reformat
2016-01-23 Adding woochi - a wifi loochi - wip from 2012
